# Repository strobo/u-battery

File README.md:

u-Battery
===========

What's this?
------------
This is Mobile USB battery Unit.

This repo includes eagle .sch/.brd file and cortex-m0 source code.

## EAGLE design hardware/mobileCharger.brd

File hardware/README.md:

u-Battery
===========

u-battery(自作モバイルブースター)を使用した際の事故等の責任は負いません
自己責任において組み立て、使用してください

組み立てのポイントなど
----------------------

###ダイオードのパターンミス
D2 D3 D4 はこのURLの部品です <http://www.digikey.jp/product-detail/ja/PMEG3050EP,115/568-6753-1-ND/2676793>
基板のパターンと部品サイズが合ってないので、スズメッキ線等を組み合わせて実装してください。

D3 D4はスルーホールが近くにあるのでそのスルーホールにハンダ付けすると楽です。

D5 D6もサイズが合ってないのでD2と同様にスズメッキ線と組み合わせて実装してください。

###チップ部品のサイズ
チップ抵抗、チップコンデンサは基本1608サイズ(日本式表記)です。
アメリカだと1608を0603と表記するので間違えないように

###温度センサ
IC3はバッテリー温度を監視するセンサを実装するパターンです。
秋月のCMOS温度センサーS-8120Cを実装できます。
<http://akizukidenshi.com/catalog/g/gI-04574/>

自分はこの温度センサの実装はしていません。センサの信号を読み取るプログラムも作ってないですw

温度センサは勝手に実装しても構いません。ただし、温度センサの信号を読み取るプログラムを追加しなければいけません。

###R5について
電流監視用の抵抗ですがIC1のOPアンプが注文ミスにより実装不可能となったため、R5はそのままジャンパでショートさせてください。

###実装しなくていい部品
OPアンプ周辺の抵抗、コンデンサは実装する必要はないです。
lpc1114のクロック回路も実装不要です。

* R3 R7 R8 R9 R10 R11 R51
* C3 C27 C28 C31
* Y1

###その他
* **partslist.txt**にどこにどの部品を実装すればいいか書かれています
* チップICの実装はフラックスを使った方がいい。というか使うべき
* R35からR44までの抵抗ですが471Ωから500Ωぐらいかな
* 当然ですが背の低い部品、小さい部品からハンダ付けしていかないと後で面倒なことになるので注意
* 完成イメージは **IMG_20130329_181824.jpg**と **IMG_20130329_230819.jpg**です
* あとは **assembly-guide.jpg**をみてください

###回路について
充電回路はマイコン(LPC1114)からON/OFFの制御ができます。
これをONにしたらバッテリーが充電されるよう設計していますが、バッテリを接続した状態でONにしたことがないので一応注意してください。ONにしなければ全く問題ないです。

OPアンプはサイズのミスで実装できないですが、基板のパターンに合う(SOP-8サイズ)のOPアンプを各自で買ってきて実装するのは問題ないです。
TLV272と似た仕様のOPアンプなら大丈夫だと思う(ちょっと自信ない)
その場合、OPアンプからのアナログ電圧を読みとるプログラムが書かれていないのでプログラムを自分で変更する必要があります。

完成イメージのSJ2にはチップコンデンサが実装されていますが、これは実装しなくても問題ないです
同じく完成イメージのC22も実装されていませんが、これはC23と同様に電解コンデンサを90°に曲げて実装してください。実装しなくても動いてるけどねw

LEDアレイの抵抗R35からR44は画像だといろんな値の抵抗が実装されていますが、これは抵抗の数が不足したので使えそうな抵抗を寄せ集めて実装したためです。471Ωから500Ωぐらいの抵抗なら問題ないです。

###電源投入手順とか電源OFF時の挙動とか
この装置は電源スイッチがありません。さらにバッテリーをつないだだけでは電源は入りません。電源を入れるには15VをDCinに接続してください。15VをDCinに接続したときに、バッテリーが接続されていてある程度の電圧があれば、15VをDCinがら抜いてもバッテリーの電力で動作し続けます。

電源OFFはバッテリーの電圧が設定値を下回ったら自動で電源が落とされます。電源が落ちているときも多少の電流が流れているので、念のためバッテリーのコネクタは基板から外しておいてください。

この辺はあまりイケてない仕様なのでバージョン2を作る機会があれば改善したい。

###バッテリーも買うなら
バッテリーを買わなくてもただの5V DC-DCコンバータとして使ってもOKです。
もしバッテリーを買うならバッテリーの発熱、発火、爆発には十分注意してください。
充電器も買ってください、基板に実装されている充電回路は動かしていのでまだ信頼性が低いです。

バッテリーと充電器を買うならこのアダプタも買った方がいいです。
<http://www.hobbyking.com/hobbyking/store/__18099__HXT_4MM_to_Banana_Plug_Charge_Lead_Adapter.html>
充電器にはこのアダプタが付属していないのでないと充電が面倒です。

バッテリーはリチウムポリマー電池で。3セル直列の11.1Vのものを使用してください。容量は自由です。

###使用している主なパーツのデータシート
#####リチウムポリマーバッテリー
*Turnigy 5000mAh 3S 25C Lipo Pack* <http://www.hobbyking.com/hobbyking/store/uh_viewItem.asp?idProduct=9183>

#####充電器
*Turnigy Accucel-6 50W 6A Balancer/Charger w/ accessories* <http://www.hobbyking.com/hobbyking/store/__7028__Turnigy_Accucel_6_50W_6A_Balancer_Charger_w_accessories.html>

#####MainController
*LPC1114* <http://ics.nxp.com/support/documents/microcontrollers/pdf/user.manual.lpc11xx.lpc11cxx.jp.pdf>

#####DC-DC Converter
*BD9876* IntFET sync 3A <http://rohmfs.rohm.com/jp/products/databook/datasheet/ic/power/switching_regulator/bd9876efj-j.pdf>

#####BatteryCharger
*MAX1873SEEE+* <http://datasheets.maxim-ic.com/jp/ds/MAX1873_jp.pdf>

#####バッテリー監視IC
*BQ29312A*
<http://www.tij.co.jp/jp/lit/ds/symlink/bq29312a.pdf>
<http://www.tij.co.jp/jp/lit/an/slua375/slua375.pdf>

#####Inductor
*NS12565T150MN* 15uH 4.33A
<http://www.digikey.jp/product-detail/ja/NS12565T150MN/587-2745-1-ND/2573939>

#####Pch-MOSFET
*SI4435DDY* <http://www.digikey.jp/product-detail/ja/SI4435DDY-T1-GE3/SI4435DDY-T1-GE3CT-ND/1978995>

#####Nch-MOSFET
*BSH105,215* <http://www.digikey.jp/product-detail/ja/BSH105,215/568-6215-1-ND/2531502>

#####OPアンプ
*TLV272* <http://www.tij.co.jp/product/jp/TLV272>

###メモ
開発時のメモです

    DSG/CHG meams BQ29312A Pin State L/H. It's not FET State
                                Disconnect DCin
     +--------------------------------------------------------------------------------------------------------+
     v          Use             Connect DCin                                                                  |
    BAT  :Full ----> BAT  :Low ---------------> BAT check mode ---------------------> BAT  :Charging -------->|
    DCin :0v         DCin :0v                   BAT  :unknown    |  BAT need          DCin :15v               |
    5Vout:on         5Vout:off                  DCin :15v        |   to charge        5Vout:on                |
    DSG  :Low        DSG  :Low                  5Vout:off        |                    DSG  :-(Low)Recommend   |
    CHG  :-          CHG  :-                    DSG  :Low        |                    CHG  :Low               |
                      |                         CHG  :-          |                     |                      |
                      | reach BAT Low limit      ^               |                     | BAT is full          |
                      v                          |               |                     v                      |
                     BAT save mode or Power down |               +------------------> BAT  :Full -------------+
                     DCin  0v                    |                  BAT doesn't       DCin :15V
                     5Vout off                   |                   need to charge   5Vout:on
                     DSG   Hi                    |                                    DSG  :-(Low)Recommend
                     CHG   -                     |                                    CHG  :Hi
                     REG   0v                    |
                     Host MCU is down            |
                      |                          |
                      +--------------------------+
                               Connect DCin

    DCinがつながっているならCHGはBATの状態に応じて決めなければならない BAT Full: Hi, BAT Low: Low
    DCinが繋がってないならCHGの状態はどっちでもいい

    DSGは基本LowにするHiにするとシステム全体が落ちる。なので、BATが最低電圧に到達した時のみHiにする
    全体が落ちているときはDCinを繋ぐと復旧する。それ以外の方法では復旧できない。
    復旧直後はBATチェックモードに入りDSGをLowにした上でBATの状態を調べる
    Hi=FET:off Low=FET:on

プログラムは完璧に上の図の通りには動作してないです。充電関係が上の図と違うはず。

解決すべき問題点や基板の設計ミスなどがたくさんあるので。気が向いたらバージョン2も作ってみたい。

組み立てに関して伝えなきゃいけないことは大体書いたと思います。もし質問等ありましたら、@_stroboまでお願いします

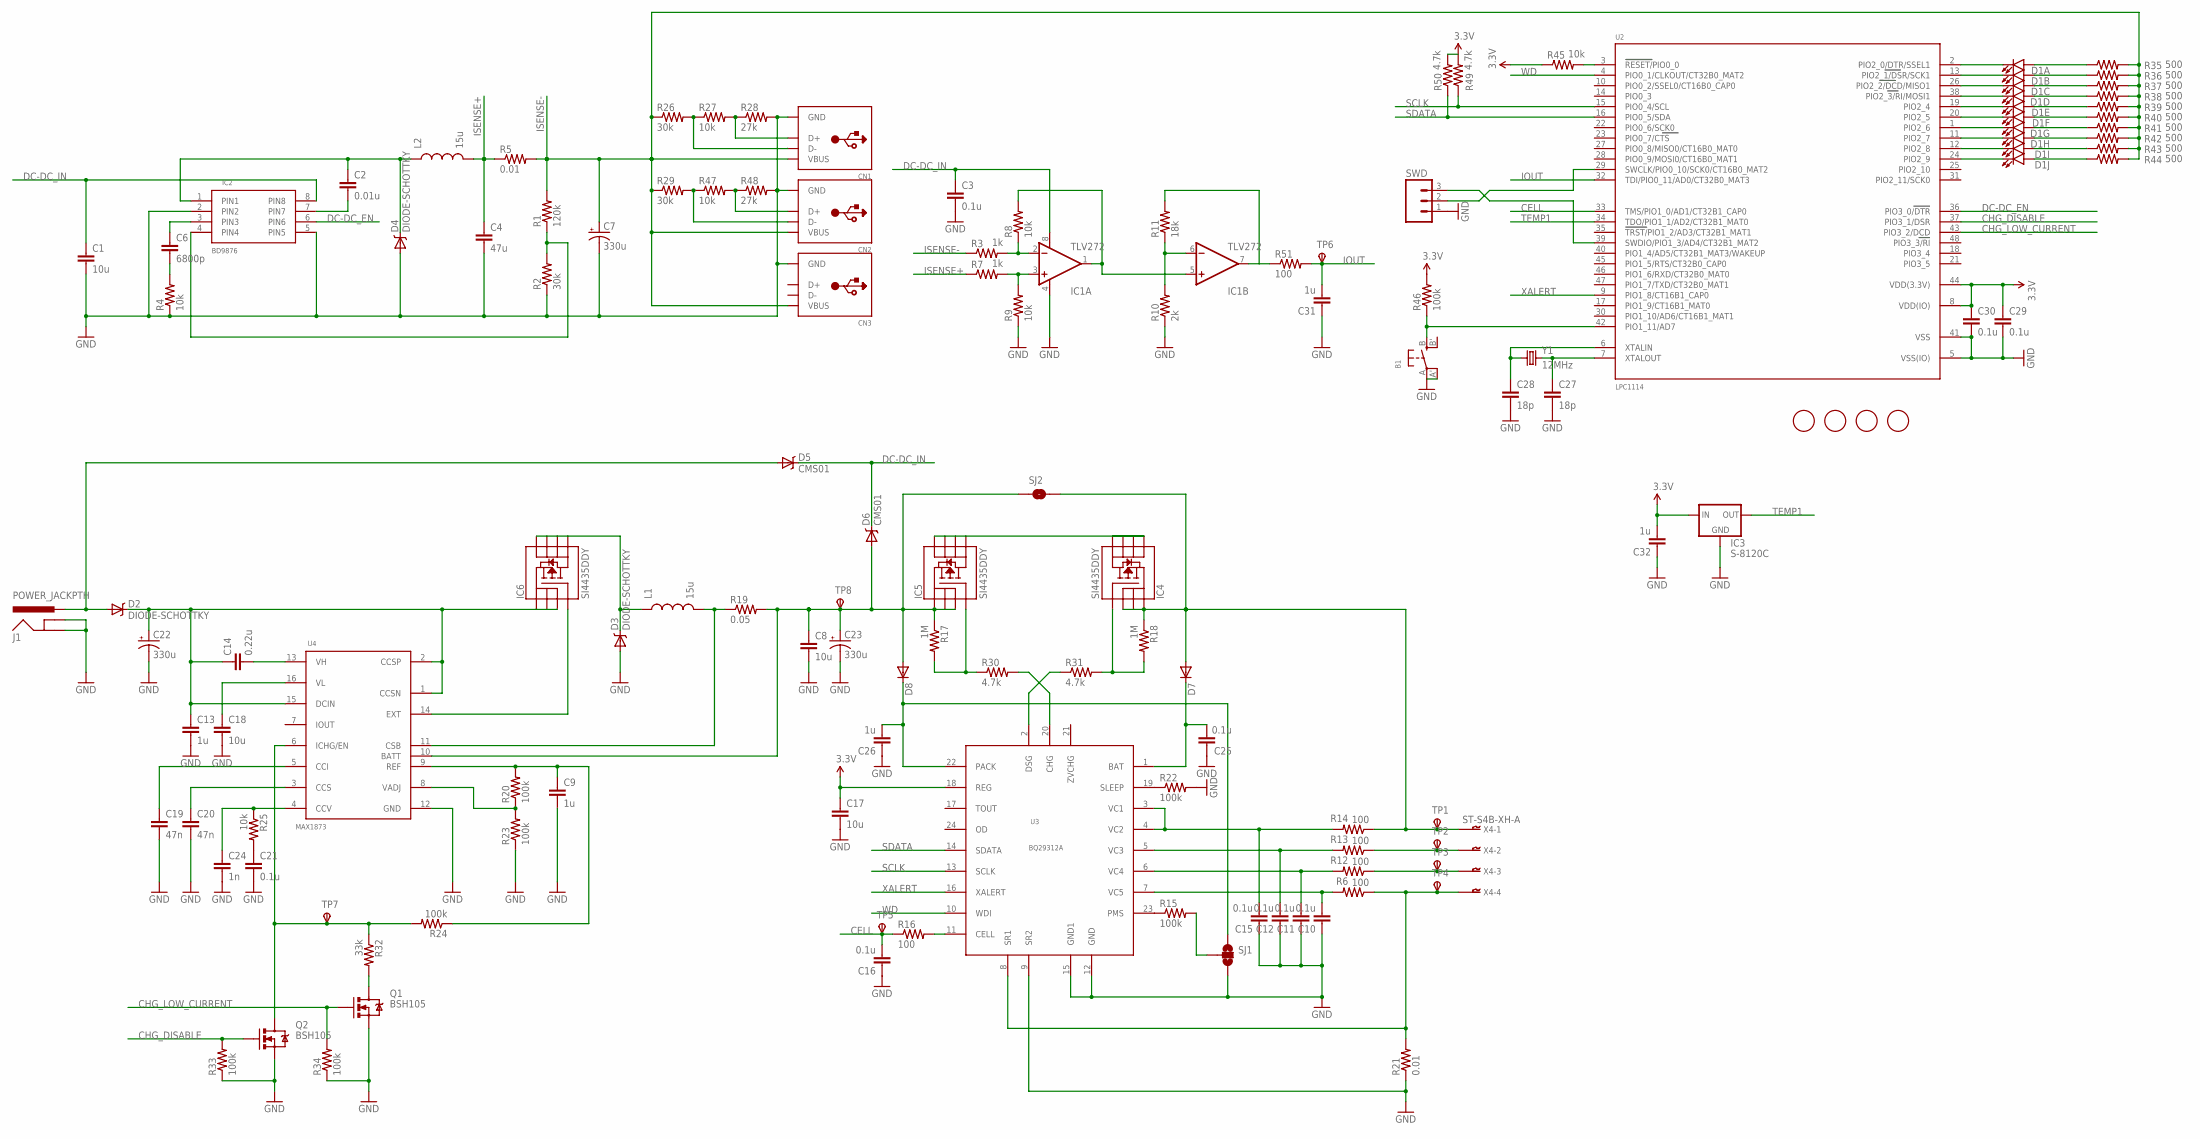
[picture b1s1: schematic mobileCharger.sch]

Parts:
B1: SWITCH_TACT_SMT; EVQ-Q2
C1, C8, C17, C18: 10u; 0805
C2: 0.01u; 0603-CAP
C3, C10, C11, C12, C15, C16, C21, C25, C29, C30: 0.1u; 0603-CAP
C4: 47u; 1206
C6: 6800p; 0603-CAP
C7: 330u; CPOL-RADIAL-100UF-25V
C9, C13, C26, C31, C32: 1u; 0603-CAP
C14: 0.22u; 0603-CAP
C19, C20: 47n; 0603-CAP
C22, C23: 330u; E3,5-8
C24: 1n; 0603-CAP
C27, C28: 18p; 0603-CAP
CN1, CN2, CN3: USB_TYPEAPTHFML; USB_HOST-PTH
D1: LED_BARGRAPH_10; LED_BARGAPH_10
D2, D3, D4: DIODE-SCHOTTKY; SOD-128
D5, D6: CMS01; M-FLAT
D7, D8: DIODESOD523; SOD523
IC1: TLV272; SO08
IC2: BD9876; SO08
IC3: S-8120C; SC-82AB
IC4, IC5, IC6: SI4435DDY; SO08
J1: POWER_JACKPTH; POWER_JACK_PTH
L1, L2: 15u; CDRH125
Q1, Q2: BSH105; SOT23-3
R1: 120k; 0603-RES
R2, R26, R29: 30k; 0603-RES
R3, R7: 1k; 0603-RES
R4, R8, R9, R25, R27, R45, R47: 10k; 0603-RES
R5, R21: 0.01; R1206
R6, R12, R13, R14, R16, R51: 100; 0603-RES
R10: 2k; 0603-RES
R11: 18k; 0603-RES
R15, R20, R22, R23, R24, R33, R34, R46: 100k; 0603-RES
R17, R18: 1M; 0603-RES
R19: 0.05; R2512
R28, R48: 27k; 0603-RES
R30, R31, R49, R50: 4.7k; 0603-RES
R32: 33k; 0603-RES
R35, R36, R37, R38, R39, R40, R41, R42, R43, R44: 500; 0603-RES
SJ1: SOLDERJUMPER_2WAYT; SJ_2
SJ2: SOLDERJUMPERNO; SJ_2S-NO
SWD: M03PTH; 1X03
TP1, TP2, TP3, TP4, TP5, TP6, TP7, TP8: TPSPAD1-13; P1-13
U2: LPC1114; LQFP48
U3: BQ29312A; TSSOP-24
U4: MAX1873; TSSOP16
U$1, U$2, U$3, U$7: MOUNTINGHOLE2.0; MOUNTINGHOLE_2.0_PLATED
X4: ST-S4B-XH-A; B4B-XH
Y1: 12MHz; HC49UP

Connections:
3.3V: C17.1, C29.1, C30.1, C32.2, IC3.P$1 (IN), R45.1, R46.2, R49.2, R50.2, U2.8 (VDD(IO)), U2.44 (VDD(3.3V)), U3.18 (REG)
CELL: C16.2, R16.1, TP5.TP, U2.33 (TMS/PIO1_0/AD1/CT32B1_CAP0)
CHG_DISABLE: Q2.1 (G), R33.2, U2.37 (PIO3_1/DSR)
CHG_LOW_CURRENT: Q1.1 (G), R34.2, U2.43 (PIO3_2/DCD)
DC-DC_EN: IC2.6 (PIN6), U2.36 (PIO3_0/DTR)
DC-DC_IN: C1.1, C3.1, D5.P$2 (C), D6.P$2 (C), IC1.8 (V+), IC2.8 (PIN8)
GND: B1.A, B1.A' (P1), C1.2, C3.2, C4.2, C7.2 (-), C8.2, C9.2, C10.1, C11.1, C12.1, C13.2, C15.1, C16.1, C17.2, C18.2, C19.2, C20.2, C21.2, C22.-, C23.-, C24.2, C25.1, C26.1, C27.2, C28.2, C29.2, C30.2, C31.1, C32.1, CN1.GND, CN2.GND, CN3.GND, D3.P$1 (A), D4.P$1 (A), IC1.4 (V-), IC2.2 (PIN2), IC2.5 (PIN5), IC3.P$2 (GND), J1.GND, J1.GNDBREAK, Q1.2 (S), Q2.2 (S), R2.1, R4.1, R9.1, R10.1, R21.1, R22.2, R23.1, R28.2, R33.1, R34.1, R48.2, SJ1.3, SWD.1, U2.5 (VSS(IO)), U2.41 (VSS), U3.9 (SR2), U3.12 (GND), U3.15 (GND1), U4.12 (GND)
IOUT: C31.2, R51.2, TP6.TP, U2.32 (TDI/PIO0_11/AD0/CT32B0_MAT3)
ISENSE+: C4.1, L2.2, R5.1, R7.1
ISENSE-: C7.1 (+), CN1.VBUS, CN2.VBUS, CN3.VBUS, R1.2, R3.1, R5.2, R26.1, R29.1, R35.2, R36.2, R37.2, R38.2, R39.2, R40.2, R41.2, R42.2, R43.2, R44.2
unnamed: C2.2, IC2.7 (PIN7)
unnamed: IC1.2 (-IN), R3.2, R8.1
unnamed: IC1.3 (+IN), R7.2, R9.2
unnamed: D1.1 (A), R35.1
unnamed: C2.1, D4.P$2 (C), IC2.1 (PIN1), L2.1
unnamed: IC1.6 (-IN), R10.2, R11.1
unnamed: C6.2, R4.2
unnamed: IC1.1 (OUT), IC1.5 (+IN), R8.2
unnamed: IC2.4 (PIN4), R1.1, R2.2
unnamed: C6.1, IC2.3 (PIN3)
unnamed: C9.1, R20.2, R24.1, U4.9 (REF)
unnamed: R15.2, SJ1.2
unnamed: C15.2, R14.2, U3.3 (VC1), U3.4 (VC2)
unnamed: D7.A, IC4.1 (S), IC4.2 (S), IC4.3 (S), R14.1, R18.1, SJ2.2, TP1.TP, X4.P$1
unnamed: R15.1, U3.23 (PMS)
unnamed: R16.2, U3.11 (CELL)
unnamed: C10.2, R6.2, U3.7 (VC5)
unnamed: IC4.5 (D), IC4.6 (D), IC4.7 (D), IC4.8 (D), IC5.5 (D), IC5.6 (D), IC5.7 (D), IC5.8 (D)
unnamed: C12.2, R13.2, U3.5 (VC3)
unnamed: C11.2, R12.2, U3.6 (VC4)
unnamed: R22.1, U3.19 (SLEEP)
unnamed: IC5.4 (G), R17.2, R30.1
unnamed: C26.2, D8.C, SJ1.1, U3.22 (PACK)
unnamed: IC4.4 (G), R18.2, R31.2
unnamed: C8.1, C23.+, D6.P$1 (A), D8.A, IC5.1 (S), IC5.2 (S), IC5.3 (S), R17.1, R19.2, SJ2.1, TP8.TP, U4.10 (BATT)
unnamed: R6.1, R21.2, TP4.TP, U3.8 (SR1), X4.P$4
unnamed: R20.1, R23.2, U4.8 (VADJ)
unnamed: L1.2, R19.1, U4.11 (CSB)
unnamed: Q1.3 (D), R32.2
unnamed: IC6.4 (G), U4.14 (EXT)
unnamed: Q2.3 (D), R24.2, R32.1, TP7.TP, U4.6 (ICHG/EN)
unnamed: D3.P$2 (C), IC6.5 (D), IC6.6 (D), IC6.7 (D), IC6.8 (D), L1.1
unnamed: C19.1, U4.5 (CCI)
unnamed: C20.1, U4.3 (CCS)
unnamed: C14.2, U4.13 (VH)
unnamed: C18.1, U4.16 (VL)
unnamed: C24.1, R25.1, U4.4 (CCV)
unnamed: C21.1, R25.2
unnamed: D2.P$1 (A), D5.P$1 (A), J1.PWR
unnamed: CN1.D+, R27.2, R28.1
unnamed: C13.1, C14.1, C22.+, D2.P$2 (C), IC6.1 (S), IC6.2 (S), IC6.3 (S), U4.1 (CCSN), U4.2 (CCSP), U4.15 (DCIN)
unnamed: R30.2, U3.20 (CHG)
unnamed: CN1.D-, R26.2, R27.1
unnamed: R31.1, U3.2 (DSG)
unnamed: SWD.2, U2.29 (SWCLK/PIO0_10/SCK0/CT16B0_MAT2)
unnamed: SWD.3, U2.39 (SWDIO/PIO1_3/AD4/CT32B1_MAT2)
unnamed: C25.2, D7.C, U3.1 (BAT)
unnamed: D1.2 (A), R36.1
unnamed: D1.3 (A), R37.1
unnamed: D1.4 (A), R38.1
unnamed: D1.5 (A), R39.1
unnamed: D1.6 (A), R40.1
unnamed: D1.7 (A), R41.1
unnamed: D1.9 (A), R43.1
unnamed: D1.8 (A), R42.1
unnamed: D1.10 (A), R44.1
unnamed: R45.2, U2.3 (RESET/PIO0_0)
unnamed: C28.1, U2.6 (XTALIN), Y1.1
unnamed: C27.1, U2.7 (XTALOUT), Y1.2
unnamed: D1.20 (C), U2.2 (PIO2_0/DTR/SSEL1)
unnamed: D1.19 (C), U2.13 (PIO2_1/DSR/SCK1)
unnamed: D1.18 (C), U2.26 (PIO2_2/DCD/MISO1)
unnamed: D1.17 (C), U2.38 (PIO2_3/RI/MOSI1)
unnamed: D1.16 (C), U2.19 (PIO2_4)
unnamed: D1.15 (C), U2.20 (PIO2_5)
unnamed: D1.14 (C), U2.1 (PIO2_6)
unnamed: D1.13 (C), U2.11 (PIO2_7)
unnamed: D1.12 (C), U2.12 (PIO2_8)
unnamed: D1.11 (C), U2.24 (PIO2_9)
unnamed: B1.B (S), R46.1, U2.42 (PIO1_11/AD7)
unnamed: R13.1, TP2.TP, X4.P$2
unnamed: R12.1, TP3.TP, X4.P$3
unnamed: CN2.D-, R29.2, R47.1
unnamed: CN2.D+, R47.2, R48.1
unnamed: IC1.7 (OUT), R11.2, R51.1
SCLK: R49.1, U2.15 (PIO0_4/SCL), U3.13 (SCLK)
SDATA: R50.1, U2.16 (PIO0_5/SDA), U3.14 (SDATA)
TEMP1: IC3.P$4 (OUT), U2.34 (TDO/PIO1_1/AD2/CT32B1_MAT0)
WD: U2.4 (PIO0_1/CLKOUT/CT32B0_MAT2), U3.10 (WDI)
XALERT: U2.9 (PIO1_8/CT16B1_CAP0), U3.16 (XALERT)

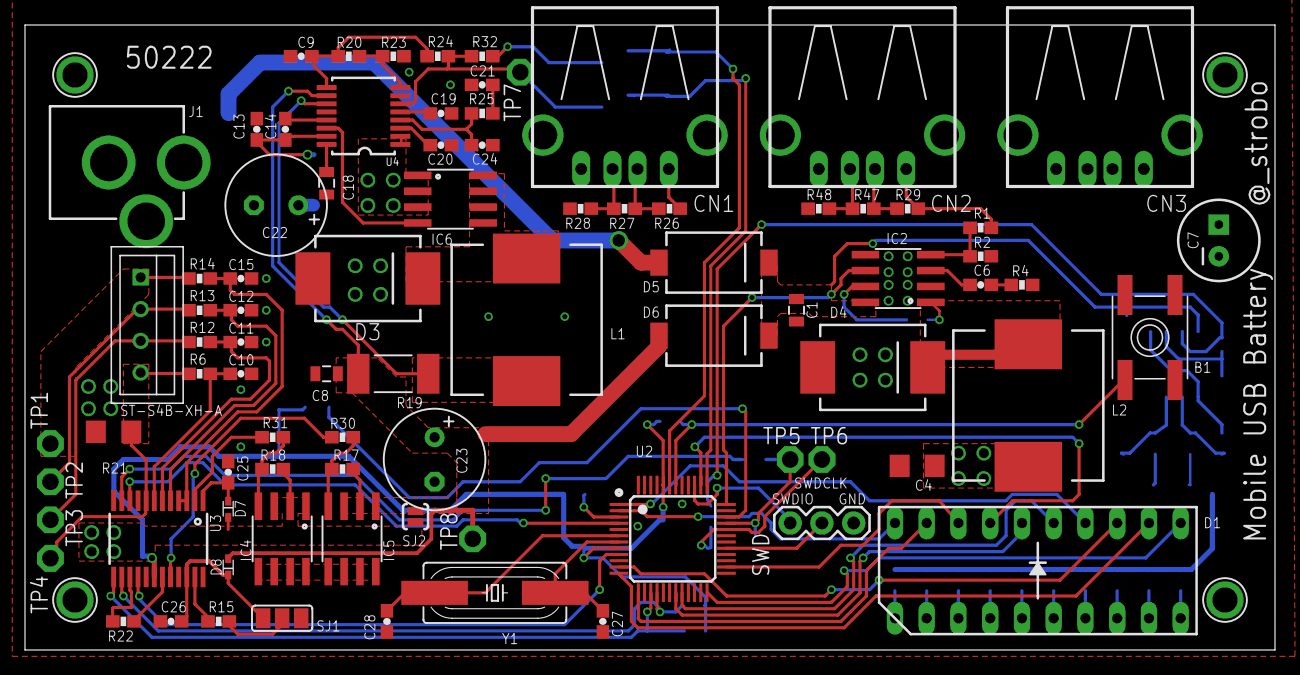
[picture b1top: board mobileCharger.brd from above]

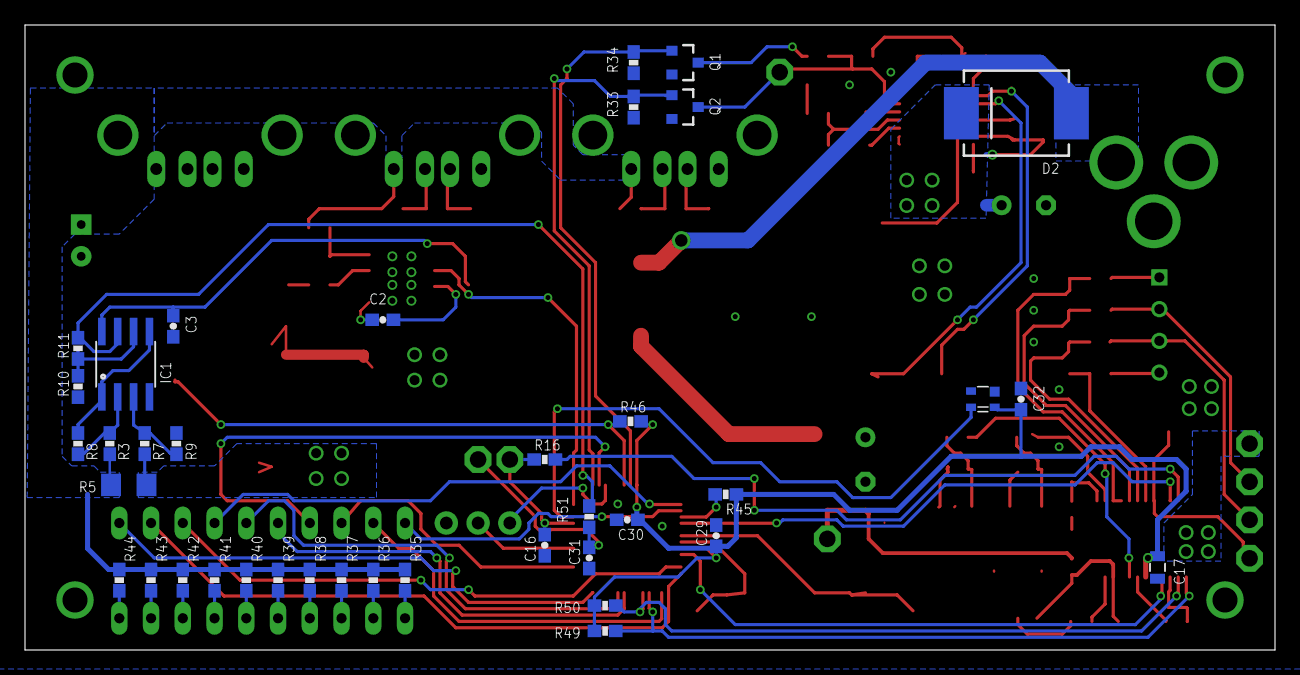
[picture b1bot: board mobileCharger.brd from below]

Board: 2 copper layers, 100.0 x 50.0 mm, 125 parts (38 on the bottom side), 90 nets.

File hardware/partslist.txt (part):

Partlist

Exported from mobileCharger.brd at 2013/03/29 19:46

EAGLE Version 6.2.0 Copyright (c) 1988-2012 CadSoft

Assembly variant: 

Part     Value           Package                 Library               Position (mm)         Orientation

B1                       EVQ-Q2                  microbuilder          (90 25)               R90
C1       10u             0805                    SparkFun-Passives     (61.722 27.178)       R270
C2       0.01u           0603-CAP                SparkFun              (71.374 26.416)       MR0
C3       0.1u            0603-CAP                SparkFun              (88.138 25.908)       MR270
C4       47u             1206                    SparkFun-Passives     (71.374 14.732)       R180
C6       6800p           0603-CAP                SparkFun              (76.454 29.21)        R0
C7       330u            CPOL-RADIAL-100UF-25V   SparkFun-Passives     (95.504 32.766)       R90
C8       10u             0805                    SparkFun-Passives     (24.13 22.098)        R180
C9       1u              0603-CAP                SparkFun              (22.098 47.498)       R180
C10      0.1u            0603-CAP                SparkFun              (17.272 22.098)       R180
C11      0.1u            0603-CAP                SparkFun              (17.272 24.638)       R180
C12      0.1u            0603-CAP                SparkFun              (17.272 27.178)       R180
C13      1u              0603-CAP                SparkFun              (18.542 41.656)       R90
C14      0.22u           0603-CAP                SparkFun              (20.828 41.656)       R90
C15      0.1u            0603-CAP                SparkFun              (17.272 29.718)       R180
C16      0.1u            0603-CAP                SparkFun              (58.42 8.382)         MR90
C17      10u             0805                    SparkFun-Passives     (9.398 6.604)         MR270
C18      10u             0805                    SparkFun-Passives     (24.13 37.338)        R270
C19      47n             0603-CAP                SparkFun              (33.274 42.926)       R0
C20      47n             0603-CAP                SparkFun              (33.274 40.386)       R0
C21      0.1u            0603-CAP                SparkFun              (36.576 45.212)       R180
C22      330u            E3,5-8                  rcl                   (20.092 35.582)       R180
C23      330u            E3,5-8                  rcl                   (32.766 15.24)        R270
C24      1n              0603-CAP                SparkFun              (36.576 40.386)       R0
C25      0.1u            0603-CAP                SparkFun              (16.256 14.224)       R270
C26      1u              0603-CAP                SparkFun              (11.684 2.286)        R0
C27      18p             0603-CAP                SparkFun              (46.228 2.286)        R270
C28      18p             0603-CAP                SparkFun              (28.956 2.286)        R270
C29      0.1u            0603-CAP                SparkFun              (44.704 9.144)        MR90
C30      0.1u            0603-CAP                SparkFun              (51.816 10.414)       MR180
C31      1u              0603-CAP                SparkFun              (54.864 7.366)        MR90
C32      1u              0603-CAP                SparkFun              (20.32 20.066)        MR270
CN1                      USB_HOST-PTH            microbuilder          (48 45)               R180
CN2                      USB_HOST-PTH            microbuilder          (67 45)               R180
CN3                      USB_HOST-PTH            microbuilder          (86 45)               R180
D1                       LED_BARGAPH_10          SparkFun-LED          (81.026 6.35)         R0
D2       DIODE-SCHOTTKY  SOD-128                 strobo-lib            (20.69 42.944)        MR180
D3       DIODE-SCHOTTKY  SOD-128                 strobo-lib            (27.432 29.718)       R0
D4       DIODE-SCHOTTKY  SOD-128                 strobo-lib            (67.818 22.606)       R0
D5       CMS01           M-FLAT                  strobo-lib            (55.118 30.988)       R0
D6       CMS01           M-FLAT                  strobo-lib            (55.118 25.146)       R0
D7                       SOD523                  SparkFun-DiscreteSemi (16.256 11.303)       R270
D8                       SOD523                  SparkFun-DiscreteSemi (16.256 6.604)        R90
IC1      TLV272          SO08                    SparkFun              (91.948 22.86)        MR0
IC2      BD9876          SO08                    strobo-lib            (69.85 29.718)        R90
IC3      S-8120C         SC-82AB                 strobo-lib            (23.368 20.066)       MR90
IC4      SI4435DDY       SO08                    SparkFun-DiscreteSemi (20.574 8.89)         R180
IC5      SI4435DDY       SO08                    SparkFun-DiscreteSemi (26.162 8.89)         R180
IC6      SI4435DDY       SO08                    SparkFun-DiscreteSemi (34.036 36.068)       R270
J1       POWER_JACKPTH   POWER_JACK_PTH          SparkFun-Connectors   (-1 39)               R270
L1       15u             CDRH125                 SparkFun-Passives     (40.132 26.416)       R0
L2       15u             CDRH125                 SparkFun-Passives     (80.264 19.558)       R0
Q1       BSH105          SOT23-3                 SparkFun-DiscreteSemi (47.244 46.99)        MR270
Q2       BSH105          SOT23-3                 SparkFun-DiscreteSemi (47.244 43.434)       MR270
R1       120k            0603-RES                SparkFun              (76.454 33.782)       R0
R2       30k             0603-RES                SparkFun              (76.454 31.496)       R180
R3       1k              0603-RES                SparkFun              (93.218 16.51)        MR90
R4       10k             0603-RES                SparkFun-Passives     (79.756 29.21)        R180
R5       0.01            R1206                   rcl                   (91.694 13.208)       MR180
R6       100             0603-RES                SparkFun              (13.97 22.098)        R0
R7       1k              0603-RES                SparkFun              (90.424 16.51)        MR90
R8       10k             0603-RES                SparkFun              (95.758 16.51)        MR90
R9       10k             0603-RES                SparkFun              (87.884 16.51)        MR270
R10      2k              0603-RES                SparkFun              (95.758 21.082)       MR90
R11      18k             0603-RES                SparkFun              (95.758 24.13)        MR90
R12      100             0603-RES                SparkFun              (13.97 24.638)        R0
R13      100             0603-RES                SparkFun              (13.97 27.178)        R0
R14      100             0603-RES                SparkFun              (13.97 29.718)        R0
R15      100k            0603-RES                SparkFun              (15.494 2.286)        R0
R16      100             0603-RES                SparkFun              (58.42 15.24)         MR0
R17      1M              0603-RES                SparkFun              (25.4 14.478)         R180
R18      1M              0603-RES                SparkFun              (19.812 14.478)       R180
R19      0.05            R2512                   resistor              (29.464 22.098)       R180
R20      100k            0603-RES                SparkFun              (25.908 47.498)       R180
R21      0.01            R1206                   rcl                   (7.086 17.452)        R0
R22      100k            0603-RES                SparkFun              (7.874 2.286)         R180
R23      100k            0603-RES                SparkFun              (29.464 47.498)       R180
R24      100k            0603-RES                SparkFun              (33.02 47.498)        R0
R25      10k             0603-RES                SparkFun              (36.576 42.926)       R0
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
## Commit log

2012-09-06 add README.md and eagle files
2012-09-08 add functions to BQ29312A into sleep mode
2013-03-29 added assembly guide files
2013-03-29 fix typo

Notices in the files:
parts and their libraries:
SparkFun-LED: Licensing: CC v3.0 Share-Alike You are welcome to use this library for commercial purposes.
